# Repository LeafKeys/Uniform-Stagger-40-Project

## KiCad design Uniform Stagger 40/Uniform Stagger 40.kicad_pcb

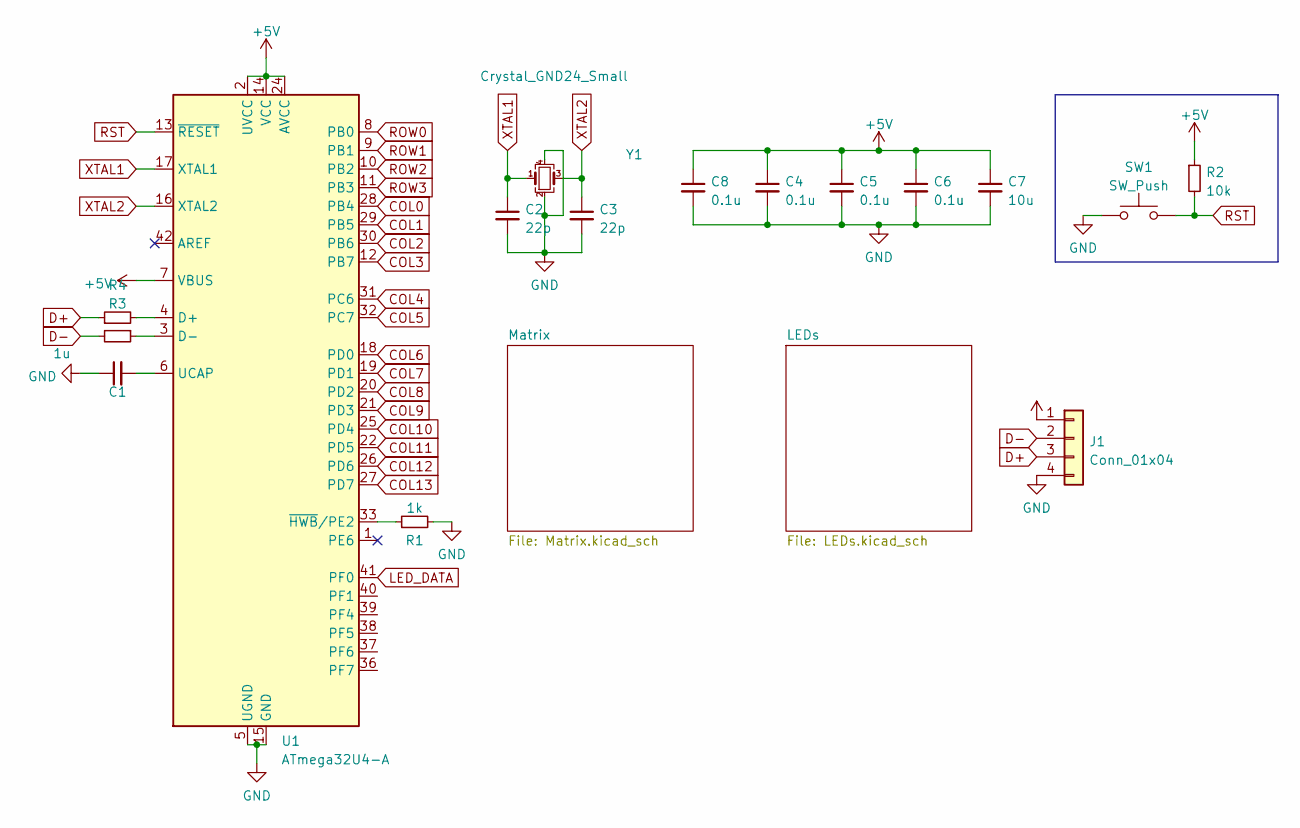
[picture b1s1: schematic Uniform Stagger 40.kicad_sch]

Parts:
C1: 1u; C_0805_2012Metric
C2, C3: 22p; C_0805_2012Metric
C4, C5, C6, C8: 0.1u; C_0805_2012Metric
C7: 10u; C_0805_2012Metric
J1: Conn_01x04; JST_SH_SM04B-SRSS-TB_1x04-1MP_P1.00mm_Horizontal
R1: 1k; R_0805_2012Metric
R2: 10k; R_0805_2012Metric
R3, R4: (no value)
SW1: SW_Push; SW_SPST_SKQG_WithStem
U1: ATmega32U4-A; TQFP-44_10x10mm_P0.8mm
Y1: Crystal_GND24_Small; Crystal_SMD_3225-4Pin_3.2x2.5mm

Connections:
+5V: C4.1, C5.1, C6.1, C7.1, C8.1, J1.1, R2.1, U1.2 (UVCC), U1.7 (VBUS), U1.14 (VCC), U1.24 (AVCC), U1.34 (VCC), U1.44 (AVCC); also elsewhere on the board
COL0: U1.28 (PB4); also elsewhere on the board
COL1: U1.29 (PB5); also elsewhere on the board
COL2: U1.30 (PB6); also elsewhere on the board
COL3: U1.12 (PB7); also elsewhere on the board
COL4: U1.31 (PC6); also elsewhere on the board
COL5: U1.32 (PC7); also elsewhere on the board
COL6: U1.18 (PD0); also elsewhere on the board
COL7: U1.19 (PD1); also elsewhere on the board
COL8: U1.20 (PD2); also elsewhere on the board
COL9: U1.21 (PD3); also elsewhere on the board
COL10: U1.25 (PD4); also elsewhere on the board
COL11: U1.22 (PD5); also elsewhere on the board
COL12: U1.26 (PD6); also elsewhere on the board
COL13: U1.27 (PD7); also elsewhere on the board
D+: J1.3, R4.1
D-: J1.2, R3.2
GND: C1.1, C2.2, C3.2, C4.2, C5.2, C6.2, C7.2, C8.2, J1.4, R1.2, SW1.1, U1.5 (UGND), U1.15 (GND), U1.23 (GND), U1.35 (GND), U1.43 (GND), Y1.2, Y1.4; also elsewhere on the board
LED_DATA: U1.41 (PF0); also elsewhere on the board
unnamed: C1.2, U1.6 (UCAP)
unnamed: R1.1, U1.33 (~HWB/PE2)
unnamed: R3.1, U1.3 (D-)
unnamed: R4.2, U1.4 (D+)
ROW0: U1.8 (PB0); also elsewhere on the board
ROW1: U1.9 (PB1); also elsewhere on the board
ROW2: U1.10 (PB2); also elsewhere on the board
ROW3: U1.11 (PB3); also elsewhere on the board
RST: R2.2, SW1.2, U1.13 (~RESET)
XTAL1: C2.1, U1.17 (XTAL1), Y1.1
XTAL2: C3.1, U1.16 (XTAL2), Y1.3

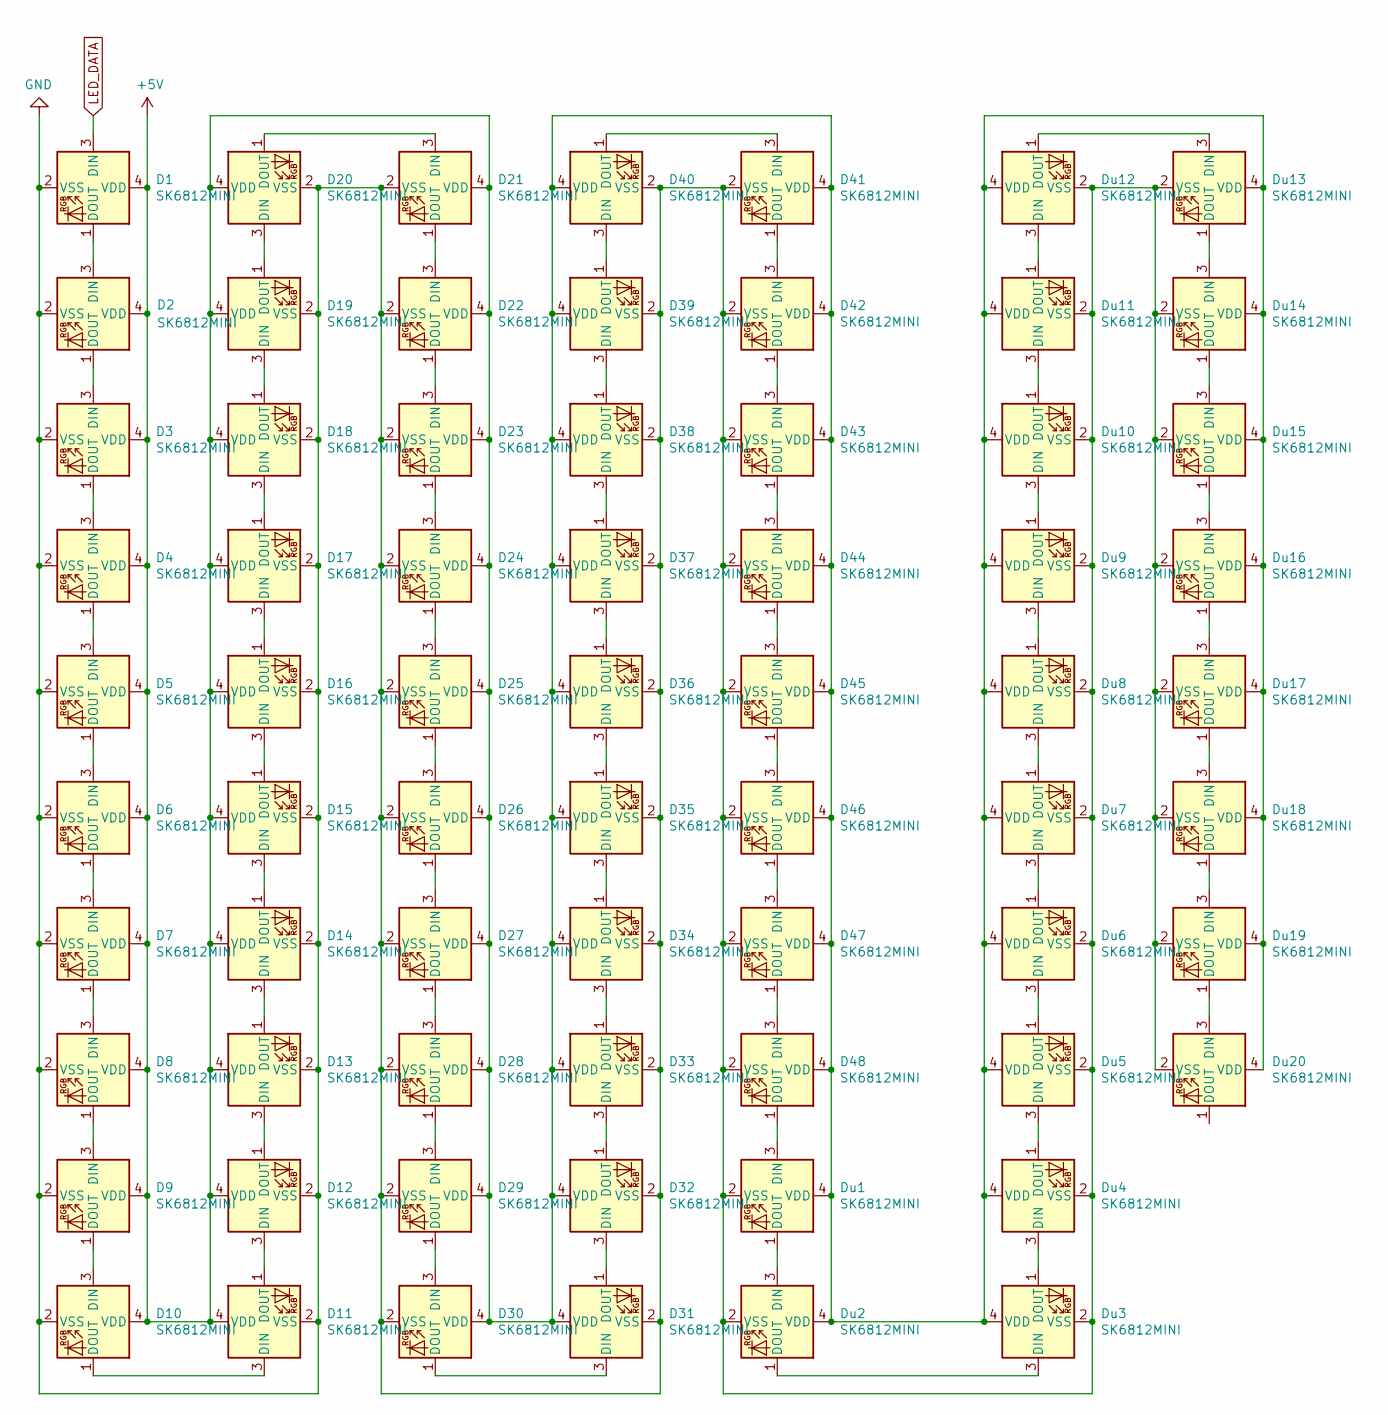
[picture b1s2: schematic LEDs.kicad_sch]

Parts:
D1, D2, D3, D4, D5, D6, D7, D8, D9, D10, D11, D12, D13, D14, D15, D16, D17, D18, D19, D20, D21, D22, D23, D24, D25, D26, D27, D28, D29, D30, D31, D32, D33, D34, D35, D36, D37, D38, D39, D40, D41, D42, D43, D44, D45, D46, D47, D48: SK6812MINI; SK6812-MINI-E
Du1, Du2, Du3, Du4, Du5, Du6, Du7, Du8, Du9, Du10, Du11, Du12, Du13, Du14, Du15, Du16, Du17, Du18, Du19, Du20: SK6812MINI; WS2812B-4020

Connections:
+5V: D1.4 (VDD), D2.4 (VDD), D3.4 (VDD), D4.4 (VDD), D5.4 (VDD), D6.4 (VDD), D7.4 (VDD), D8.4 (VDD), D9.4 (VDD), D10.4 (VDD), D11.4 (VDD), D12.4 (VDD), D13.4 (VDD), D14.4 (VDD), D15.4 (VDD), D16.4 (VDD), D17.4 (VDD), D18.4 (VDD), D19.4 (VDD), D20.4 (VDD), D21.4 (VDD), D22.4 (VDD), D23.4 (VDD), D24.4 (VDD), D25.4 (VDD), D26.4 (VDD), D27.4 (VDD), D28.4 (VDD), D29.4 (VDD), D30.4 (VDD), D31.4 (VDD), D32.4 (VDD), D33.4 (VDD), D34.4 (VDD), D35.4 (VDD), D36.4 (VDD), D37.4 (VDD), D38.4 (VDD), D39.4 (VDD), D40.4 (VDD), D41.4 (VDD), D42.4 (VDD), D43.4 (VDD), D44.4 (VDD), D45.4 (VDD), D46.4 (VDD), D47.4 (VDD), D48.4 (VDD), Du1.4 (VDD), Du2.4 (VDD), Du3.4 (VDD), Du4.4 (VDD), Du5.4 (VDD), Du6.4 (VDD), Du7.4 (VDD), Du8.4 (VDD), Du9.4 (VDD), Du10.4 (VDD), Du11.4 (VDD), Du12.4 (VDD), Du13.4 (VDD), Du14.4 (VDD), Du15.4 (VDD), Du16.4 (VDD), Du17.4 (VDD), Du18.4 (VDD), Du19.4 (VDD), Du20.4 (VDD); also elsewhere on the board
GND: D1.2 (VSS), D2.2 (VSS), D3.2 (VSS), D4.2 (VSS), D5.2 (VSS), D6.2 (VSS), D7.2 (VSS), D8.2 (VSS), D9.2 (VSS), D10.2 (VSS), D11.2 (VSS), D12.2 (VSS), D13.2 (VSS), D14.2 (VSS), D15.2 (VSS), D16.2 (VSS), D17.2 (VSS), D18.2 (VSS), D19.2 (VSS), D20.2 (VSS), D21.2 (VSS), D22.2 (VSS), D23.2 (VSS), D24.2 (VSS), D25.2 (VSS), D26.2 (VSS), D27.2 (VSS), D28.2 (VSS), D29.2 (VSS), D30.2 (VSS), D31.2 (VSS), D32.2 (VSS), D33.2 (VSS), D34.2 (VSS), D35.2 (VSS), D36.2 (VSS), D37.2 (VSS), D38.2 (VSS), D39.2 (VSS), D40.2 (VSS), D41.2 (VSS), D42.2 (VSS), D43.2 (VSS), D44.2 (VSS), D45.2 (VSS), D46.2 (VSS), D47.2 (VSS), D48.2 (VSS), Du1.2 (VSS), Du2.2 (VSS), Du3.2 (VSS), Du4.2 (VSS), Du5.2 (VSS), Du6.2 (VSS), Du7.2 (VSS), Du8.2 (VSS), Du9.2 (VSS), Du10.2 (VSS), Du11.2 (VSS), Du12.2 (VSS), Du13.2 (VSS), Du14.2 (VSS), Du15.2 (VSS), Du16.2 (VSS), Du17.2 (VSS), Du18.2 (VSS), Du19.2 (VSS), Du20.2 (VSS); also elsewhere on the board
LED_DATA: D1.3 (DIN); also elsewhere on the board
unnamed: D1.1 (DOUT), D2.3 (DIN)
unnamed: D2.1 (DOUT), D3.3 (DIN)
unnamed: D3.1 (DOUT), D4.3 (DIN)
unnamed: D4.1 (DOUT), D5.3 (DIN)
unnamed: D5.1 (DOUT), D6.3 (DIN)
unnamed: D6.1 (DOUT), D7.3 (DIN)
unnamed: D7.1 (DOUT), D8.3 (DIN)
unnamed: D8.1 (DOUT), D9.3 (DIN)
unnamed: D10.1 (DOUT), D11.3 (DIN)
unnamed: D9.1 (DOUT), D10.3 (DIN)
unnamed: D11.1 (DOUT), D12.3 (DIN)
unnamed: D12.1 (DOUT), D13.3 (DIN)
unnamed: D13.1 (DOUT), D14.3 (DIN)
unnamed: D14.1 (DOUT), D15.3 (DIN)
unnamed: D15.1 (DOUT), D16.3 (DIN)
unnamed: D16.1 (DOUT), D17.3 (DIN)
unnamed: D17.1 (DOUT), D18.3 (DIN)
unnamed: D18.1 (DOUT), D19.3 (DIN)
unnamed: D19.1 (DOUT), D20.3 (DIN)
unnamed: D20.1 (DOUT), D21.3 (DIN)
unnamed: D21.1 (DOUT), D22.3 (DIN)
unnamed: D22.1 (DOUT), D23.3 (DIN)
unnamed: D23.1 (DOUT), D24.3 (DIN)
unnamed: D24.1 (DOUT), D25.3 (DIN)
unnamed: D25.1 (DOUT), D26.3 (DIN)
unnamed: D26.1 (DOUT), D27.3 (DIN)
unnamed: D27.1 (DOUT), D28.3 (DIN)
unnamed: D28.1 (DOUT), D29.3 (DIN)
unnamed: D29.1 (DOUT), D30.3 (DIN)
unnamed: D30.1 (DOUT), D31.3 (DIN)
unnamed: D31.1 (DOUT), D32.3 (DIN)
unnamed: D32.1 (DOUT), D33.3 (DIN)
unnamed: D33.1 (DOUT), D34.3 (DIN)
unnamed: D34.1 (DOUT), D35.3 (DIN)
unnamed: D35.1 (DOUT), D36.3 (DIN)
unnamed: D36.1 (DOUT), D37.3 (DIN)
unnamed: D37.1 (DOUT), D38.3 (DIN)
unnamed: D38.1 (DOUT), D39.3 (DIN)
unnamed: D39.1 (DOUT), D40.3 (DIN)
unnamed: D40.1 (DOUT), D41.3 (DIN)
unnamed: D41.1 (DOUT), D42.3 (DIN)
unnamed: D42.1 (DOUT), D43.3 (DIN)
unnamed: D43.1 (DOUT), D44.3 (DIN)
unnamed: D44.1 (DOUT), D45.3 (DIN)
unnamed: D45.1 (DOUT), D46.3 (DIN)
unnamed: D46.1 (DOUT), D47.3 (DIN)
unnamed: D47.1 (DOUT), D48.3 (DIN)
unnamed: D48.1 (DOUT), Du1.3 (DIN)
unnamed: Du1.1 (DOUT), Du2.3 (DIN)
unnamed: Du2.1 (DOUT), Du3.3 (DIN)
unnamed: Du3.1 (DOUT), Du4.3 (DIN)
unnamed: Du4.1 (DOUT), Du5.3 (DIN)
unnamed: Du5.1 (DOUT), Du6.3 (DIN)
unnamed: Du6.1 (DOUT), Du7.3 (DIN)
unnamed: Du7.1 (DOUT), Du8.3 (DIN)
unnamed: Du8.1 (DOUT), Du9.3 (DIN)
unnamed: Du10.1 (DOUT), Du11.3 (DIN)
unnamed: Du9.1 (DOUT), Du10.3 (DIN)
unnamed: Du11.1 (DOUT), Du12.3 (DIN)
unnamed: Du12.1 (DOUT), Du13.3 (DIN)
unnamed: Du13.1 (DOUT), Du14.3 (DIN)
unnamed: Du14.1 (DOUT), Du15.3 (DIN)
unnamed: Du15.1 (DOUT), Du16.3 (DIN)
unnamed: Du16.1 (DOUT), Du17.3 (DIN)
unnamed: Du17.1 (DOUT), Du18.3 (DIN)
unnamed: Du18.1 (DOUT), Du19.3 (DIN)
unnamed: Du19.1 (DOUT), Du20.3 (DIN)

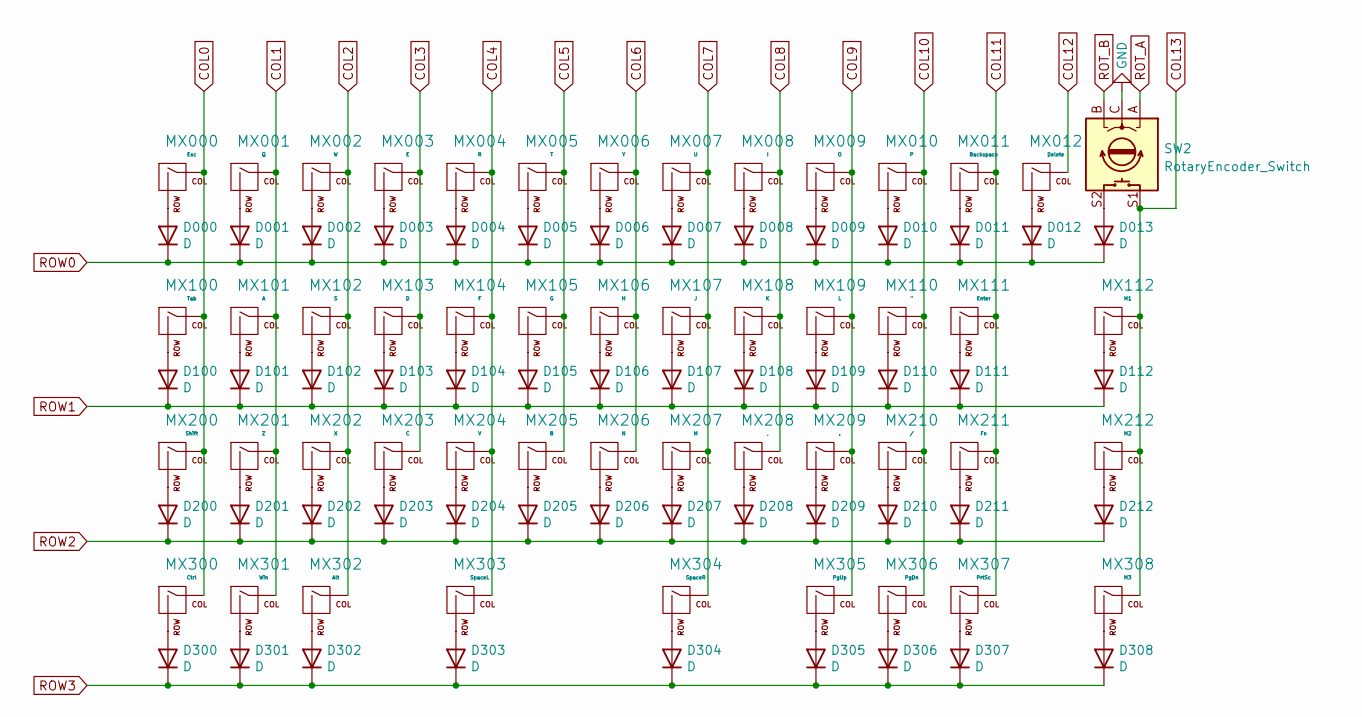
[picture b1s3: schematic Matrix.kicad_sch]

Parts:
D000, D001, D002, D003, D004, D005, D006, D007, D008, D009, D010, D011, D012, D013, D100, D101, D102, D103, D104, D105, D106, D107, D108, D109, D110, D111, D112, D200, D201, D202, D203, D204, D205, D206, D207, D208, D209, D210, D211, D212, D300, D301, D302, D303, D304, D305, D306, D307, D308: D; D_SOD-123
MX000: Esc; MXOnly-1U-Hotswap
MX001: Q; MXOnly-1U-Hotswap
MX002: W; MXOnly-1U-Hotswap
MX003: E; MXOnly-1U-Hotswap
MX004: R; MXOnly-1U-Hotswap
MX005: T; MXOnly-1U-Hotswap
MX006: Y; MXOnly-1U-Hotswap
MX007: U; MXOnly-1U-Hotswap
MX008: I; MXOnly-1U-Hotswap
MX009: O; MXOnly-1U-Hotswap
MX010: P; MXOnly-1U-Hotswap
MX011: Backspace; MXOnly-1U-Hotswap
MX012: Delete; MXOnly-1U-Hotswap
MX100: Tab; MXOnly-1.25U-Hotswap
MX101: A; MXOnly-1U-Hotswap
MX102: S; MXOnly-1U-Hotswap
MX103: D; MXOnly-1U-Hotswap
MX104: F; MXOnly-1U-Hotswap
MX105: G; MXOnly-1U-Hotswap
MX106: H; MXOnly-1U-Hotswap
MX107: J; MXOnly-1U-Hotswap
MX108: K; MXOnly-1U-Hotswap
MX109: L; MXOnly-1U-Hotswap
MX110: "; MXOnly-1U-Hotswap
MX111: Enter; MXOnly-1.75U-Hotswap
MX112: M1; MXOnly-1U-Hotswap
MX200: Shift; MXOnly-1.5U-Hotswap
MX201: Z; MXOnly-1U-Hotswap
MX202: X; MXOnly-1U-Hotswap
MX203: C; MXOnly-1U-Hotswap
MX204: V; MXOnly-1U-Hotswap
MX205: B; MXOnly-1U-Hotswap
MX206: N; MXOnly-1U-Hotswap
MX207: M; MXOnly-1U-Hotswap
MX208: ,; MXOnly-1U-Hotswap
MX209: .; MXOnly-1U-Hotswap
MX210: /; MXOnly-1U-Hotswap
MX211: Fn; MXOnly-1.5U-Hotswap
MX212: M2; MXOnly-1U-Hotswap
MX300: Ctrl; MXOnly-1.25U-Hotswap
MX301: Win; MXOnly-1.25U-Hotswap
MX302: Alt; MXOnly-1.25U-Hotswap
MX303: SpaceL; MXOnly-2.75U-Hotswap-ReversedStabilizers
MX304: SpaceR; MXOnly-2.75U-Hotswap-ReversedStabilizers
MX305: PgUp; MXOnly-1.25U-Hotswap
MX306: PgDn; MXOnly-1.25U-Hotswap
MX307: PrtSc; MXOnly-1.25U-Hotswap
MX308: M3; MXOnly-1U-Hotswap
SW2: RotaryEncoder_Switch; RotaryEncoder_Alps_EC11E-Switch_Vertical_H20mm

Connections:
COL0: MX000.1 (COL), MX100.1 (COL), MX200.1 (COL), MX300.1 (COL); also elsewhere on the board
COL1: MX001.1 (COL), MX101.1 (COL), MX201.1 (COL), MX301.1 (COL); also elsewhere on the board
COL2: MX002.1 (COL), MX102.1 (COL), MX202.1 (COL), MX302.1 (COL); also elsewhere on the board
COL3: MX003.1 (COL), MX103.1 (COL), MX203.1 (COL); also elsewhere on the board
COL4: MX004.1 (COL), MX104.1 (COL), MX204.1 (COL), MX303.1 (COL); also elsewhere on the board
COL5: MX005.1 (COL), MX105.1 (COL), MX205.1 (COL); also elsewhere on the board
COL6: MX006.1 (COL), MX106.1 (COL), MX206.1 (COL); also elsewhere on the board
COL7: MX007.1 (COL), MX107.1 (COL), MX207.1 (COL), MX304.1 (COL); also elsewhere on the board
COL8: MX008.1 (COL), MX108.1 (COL), MX208.1 (COL); also elsewhere on the board
COL9: MX009.1 (COL), MX109.1 (COL), MX209.1 (COL), MX305.1 (COL); also elsewhere on the board
COL10: MX010.1 (COL), MX110.1 (COL), MX210.1 (COL), MX306.1 (COL); also elsewhere on the board
COL11: MX011.1 (COL), MX111.1 (COL), MX211.1 (COL), MX307.1 (COL); also elsewhere on the board
COL12: MX012.1 (COL); also elsewhere on the board
COL13: MX112.1 (COL), MX212.1 (COL), MX308.1 (COL), SW2.S1; also elsewhere on the board
GND: SW2.C; also elsewhere on the board
unnamed: D000.2 (A), MX000.2 (ROW)
unnamed: D001.2 (A), MX001.2 (ROW)
unnamed: D002.2 (A), MX002.2 (ROW)
unnamed: D003.2 (A), MX003.2 (ROW)
unnamed: D004.2 (A), MX004.2 (ROW)
unnamed: D005.2 (A), MX005.2 (ROW)
unnamed: D006.2 (A), MX006.2 (ROW)
unnamed: D007.2 (A), MX007.2 (ROW)
unnamed: D008.2 (A), MX008.2 (ROW)
unnamed: D009.2 (A), MX009.2 (ROW)
unnamed: D010.2 (A), MX010.2 (ROW)
unnamed: D011.2 (A), MX011.2 (ROW)
unnamed: D012.2 (A), MX012.2 (ROW)
unnamed: D013.2 (A), SW2.S2
unnamed: D100.2 (A), MX100.2 (ROW)
unnamed: D101.2 (A), MX101.2 (ROW)
unnamed: D102.2 (A), MX102.2 (ROW)
unnamed: D103.2 (A), MX103.2 (ROW)
unnamed: D104.2 (A), MX104.2 (ROW)
unnamed: D105.2 (A), MX105.2 (ROW)
unnamed: D106.2 (A), MX106.2 (ROW)
unnamed: D107.2 (A), MX107.2 (ROW)
unnamed: D108.2 (A), MX108.2 (ROW)
unnamed: D109.2 (A), MX109.2 (ROW)
unnamed: D110.2 (A), MX110.2 (ROW)
unnamed: D111.2 (A), MX111.2 (ROW)
unnamed: D112.2 (A), MX112.2 (ROW)
unnamed: D200.2 (A), MX200.2 (ROW)
unnamed: D201.2 (A), MX201.2 (ROW)
unnamed: D202.2 (A), MX202.2 (ROW)
unnamed: D203.2 (A), MX203.2 (ROW)
unnamed: D204.2 (A), MX204.2 (ROW)
unnamed: D205.2 (A), MX205.2 (ROW)
unnamed: D206.2 (A), MX206.2 (ROW)
unnamed: D207.2 (A), MX207.2 (ROW)
unnamed: D208.2 (A), MX208.2 (ROW)
unnamed: D209.2 (A), MX209.2 (ROW)
unnamed: D210.2 (A), MX210.2 (ROW)
unnamed: D211.2 (A), MX211.2 (ROW)
unnamed: D212.2 (A), MX212.2 (ROW)
unnamed: D300.2 (A), MX300.2 (ROW)
unnamed: D301.2 (A), MX301.2 (ROW)
unnamed: D302.2 (A), MX302.2 (ROW)
unnamed: D303.2 (A), MX303.2 (ROW)
unnamed: D304.2 (A), MX304.2 (ROW)
unnamed: D305.2 (A), MX305.2 (ROW)
unnamed: D306.2 (A), MX306.2 (ROW)
unnamed: D307.2 (A), MX307.2 (ROW)
unnamed: D308.2 (A), MX308.2 (ROW)
ROT_A: SW2.A
ROT_B: SW2.B
ROW0: D000.1 (K), D001.1 (K), D002.1 (K), D003.1 (K), D004.1 (K), D005.1 (K), D006.1 (K), D007.1 (K), D008.1 (K), D009.1 (K), D010.1 (K), D011.1 (K), D012.1 (K), D013.1 (K); also elsewhere on the board
ROW1: D100.1 (K), D101.1 (K), D102.1 (K), D103.1 (K), D104.1 (K), D105.1 (K), D106.1 (K), D107.1 (K), D108.1 (K), D109.1 (K), D110.1 (K), D111.1 (K), D112.1 (K); also elsewhere on the board
ROW2: D200.1 (K), D201.1 (K), D202.1 (K), D203.1 (K), D204.1 (K), D205.1 (K), D206.1 (K), D207.1 (K), D208.1 (K), D209.1 (K), D210.1 (K), D211.1 (K), D212.1 (K); also elsewhere on the board
ROW3: D300.1 (K), D301.1 (K), D302.1 (K), D303.1 (K), D304.1 (K), D305.1 (K), D306.1 (K), D307.1 (K), D308.1 (K); also elsewhere on the board

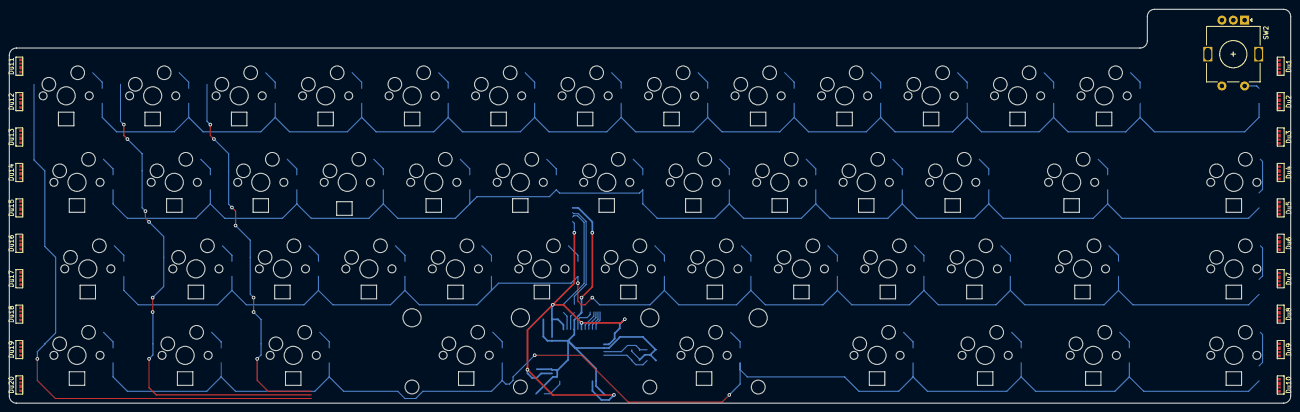
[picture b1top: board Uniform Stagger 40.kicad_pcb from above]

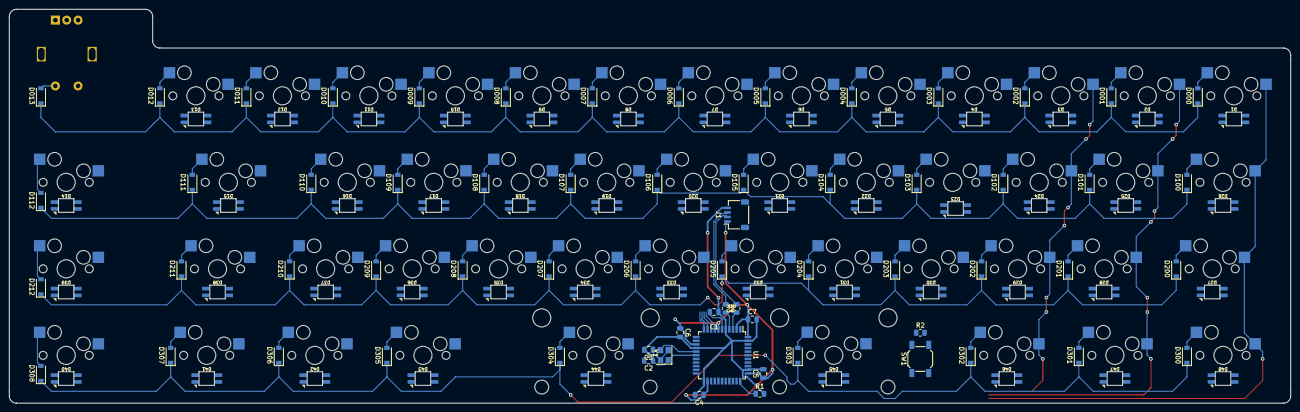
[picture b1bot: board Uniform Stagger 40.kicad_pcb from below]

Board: 2 copper layers, 282.2 x 86.7 mm, 181 parts (112 on the bottom side), 146 nets.
